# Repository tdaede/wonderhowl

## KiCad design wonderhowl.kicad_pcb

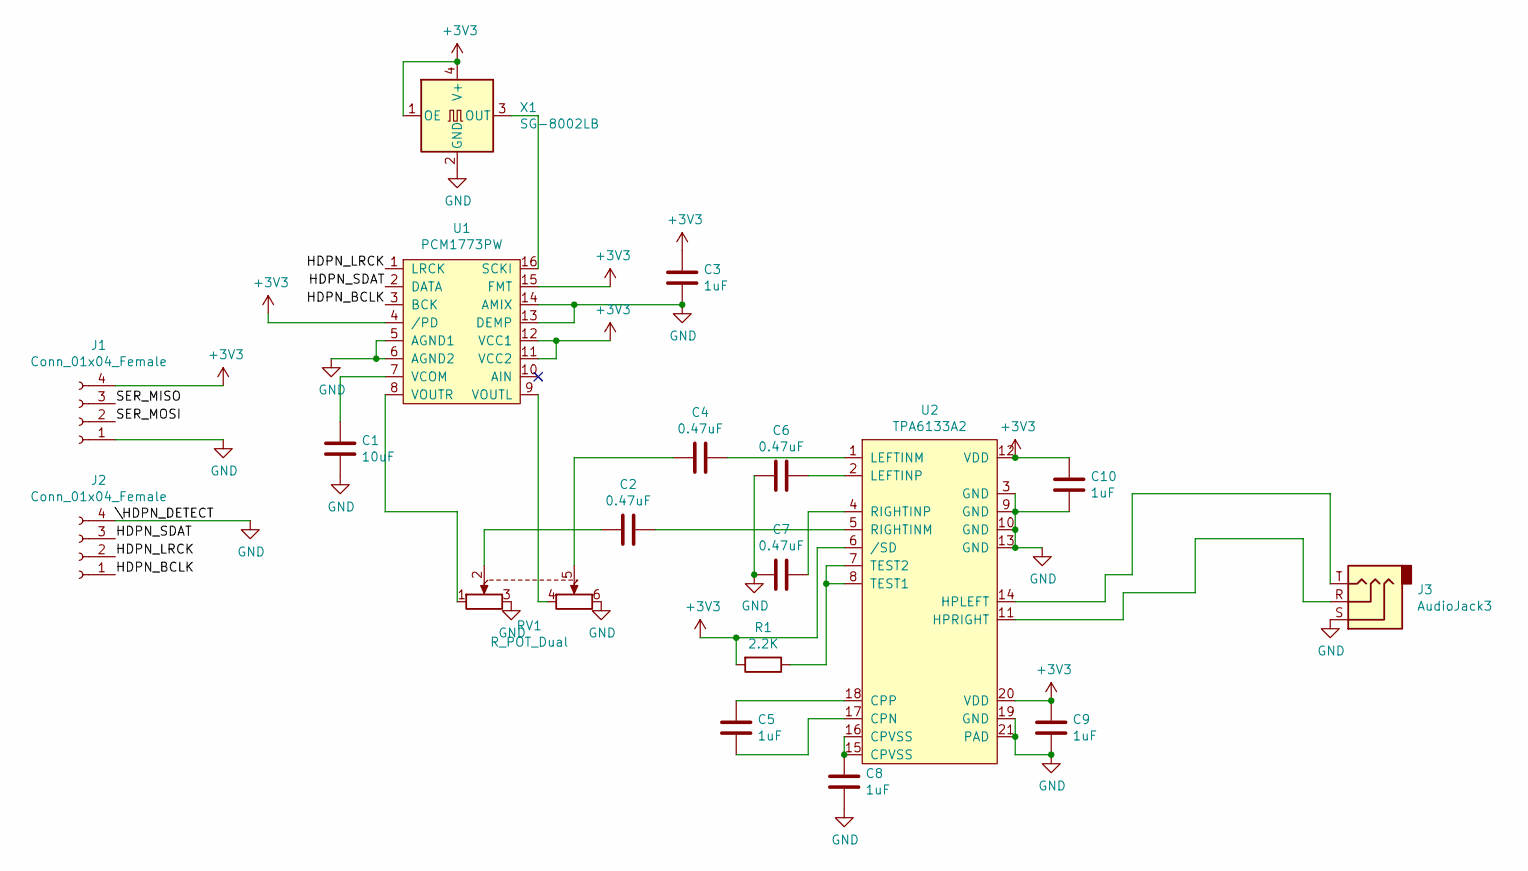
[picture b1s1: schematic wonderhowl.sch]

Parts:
C1: 10uF; C_0603_1608Metric
C2, C4, C6, C7: 0.47uF; C_0603_1608Metric
C3, C5, C8, C9, C10: 1uF; C_0603_1608Metric
J1, J2: Conn_01x04_Female; Molex_0472861001_Vertical
J3: AudioJack3; Jack_3.5mm_CUI_SJ-3523-SMT_Horizontal
R1: 2.2K; R_0603_1608Metric
RV1: R_POT_Dual; RK10J1
U1: PCM1773PW; TSSOP-16_4.4x5mm_P0.65mm
U2: TPA6133A2; Texas_S-PVQFN-N20_EP2.7x2.7mm_ThermalVias
X1: SG-8002LB; Oscillator_SMD_SeikoEpson_SG8002LB-4Pin_5.0x3.2mm

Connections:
+3V3: C3.1, C9.1, C10.1, J1.4, R1.2, U1.4 (/PD), U1.11 (VCC2), U1.12 (VCC1), U1.15 (FMT), U2.6 (/SD), U2.12 (VDD), U2.20 (VDD), X1.1 (OE), X1.4 (V+)
/HDPN_BCLK: J2.1, U1.3 (BCK)
/HDPN_LRCK: J2.2, U1.1 (LRCK)
/HDPN_SDAT: J2.3, U1.2 (DATA)
/SER_MISO: J1.3
/SER_MOSI: J1.2
GND: C1.2, C3.2, C6.1, C7.1, C8.2, C9.2, C10.2, J1.1, J2.4, J3.S, RV1.3, RV1.6, U1.5 (AGND1), U1.6 (AGND2), U1.13 (DEMP), U1.14 (AMIX), U2.3 (GND), U2.9 (GND), U2.10 (GND), U2.13 (GND), U2.19 (GND), U2.21 (PAD), X1.2 (GND)
unnamed: C1.1, U1.7 (VCOM)
unnamed: C2.1, RV1.2
unnamed: C2.2, U2.5 (RIGHTINM)
unnamed: C4.1, RV1.5
unnamed: C4.2, U2.1 (LEFTINM)
unnamed: C5.1, U2.18 (CPP)
unnamed: C5.2, U2.17 (CPN)
unnamed: C6.2, U2.2 (LEFTINP)
unnamed: C7.2, U2.4 (RIGHTINP)
unnamed: C8.1, U2.15 (CPVSS), U2.16 (CPVSS)
unnamed: J3.R, U2.11 (HPRIGHT)
unnamed: J3.T, U2.14 (HPLEFT)
unnamed: R1.1, U2.7 (TEST2), U2.8 (TEST1)
unnamed: RV1.1, U1.8 (VOUTR)
unnamed: RV1.4, U1.9 (VOUTL)
unnamed: U1.16 (SCKI), X1.3 (OUT)

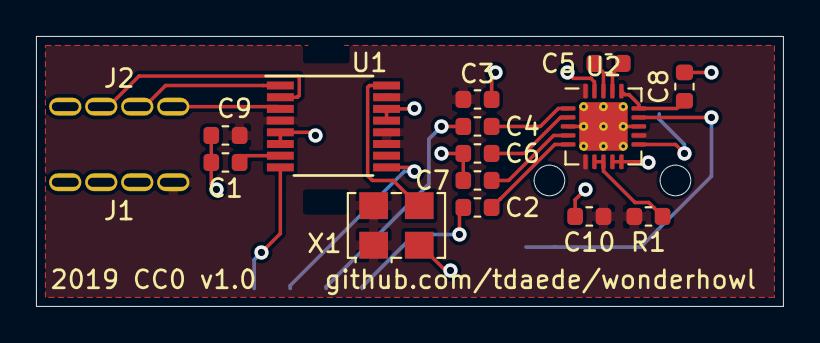
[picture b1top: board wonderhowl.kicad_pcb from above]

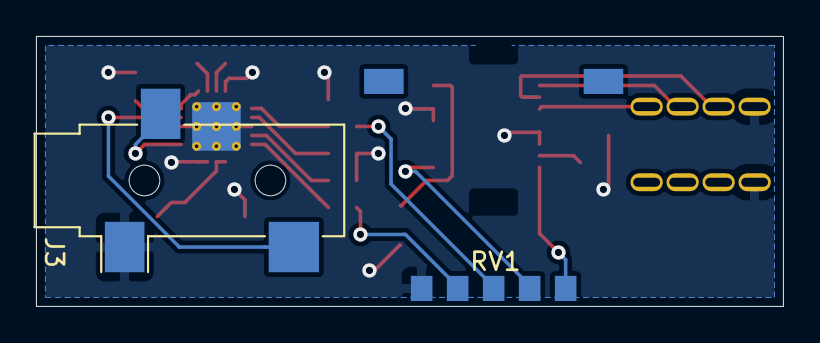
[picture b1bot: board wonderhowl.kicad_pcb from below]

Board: 2 copper layers, 41.5 x 15.0 mm, 18 parts (2 on the bottom side), 21 nets.

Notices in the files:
wonderhowl.kicad_pcb:
2019 CC0 v1.0
